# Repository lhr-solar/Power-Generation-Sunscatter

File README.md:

# :sunny: Sunscatter - Maximum Power Point Tracker Board

- [:sunny: Sunscatter - Maximum Power Point Tracker Board](#sunny-sunscatter---maximum-power-point-tracker-board)
  - [Repository Structure](#repository-structure)
  - [Maintainers](#maintainers)
  - [Versioning](#versioning)
  - [TODO](#todo)

---

## Repository Structure

- **datasheets** - contains datasheets for major components of the Sunscatter.
- **docs** - contains documentation on how to build, test, and use the Sunscatter.
- **fw** - contains fw that is loaded onto the Sunscatter.
  - **tests** - test programs used to characterize and validate the Sunscatter.
  - **src** - main program used to run the Sunscatter.
  - **inc** - internally developed libraries specific for the Sunscatter.
  - **lib** - third party libraries used by the Sunscatter.
- **hw**
  - **Footprints** - project specfic footprint association files for the Sunscatter.
  - **Models** - 3d .step files for the PCB 3d viewer.
  - **Symbols** - project specific symbol files for the Sunscatter.
  - **vX_Y_Z** - frozen versioning folder for PCB production files.
  - design files

---

## Maintainers

The current maintainer of this project is Matthew Yu as of 07/16/2023. His email
is [matthewjkyu@gmail.com](matthewjkyu@gmail.com).

Contributors to the HW and FW encompass many dedicated students, including:

- Jacob Pustilnik
- Afnan Mir
- Youssef Elsherif
- Austin Tsao
- Joseph Onofre
- Ricky Tiet
- Javier Lopez
- Chioma Okorie
- Corey Hulse
- Kaleb Todd
- Jennifer Dahm
- And many others...

Special thanks to Professor Gary Hallock, who supervised the development and
design of this project.

---

## Versioning

This PCB is on unified version `3.4.0`. Every time the schematic and/or layout
is updated, this version number should go up. We use [semantic
versioning](https://semver.org/) to denote between versions. See the
[changelog](./docs/CHANGELOG.md) for more details.

---

## TODO

Documentation

- Update assembly and testing document, ordering document, and improvement document.
- Add datasheets for key components of the device.

HW

- Transition to v4.0.0 using modified board design from MPPT-design repo
- Clean up files in hw folder

SW

- Regenerate code for MBED with proposed filestructure

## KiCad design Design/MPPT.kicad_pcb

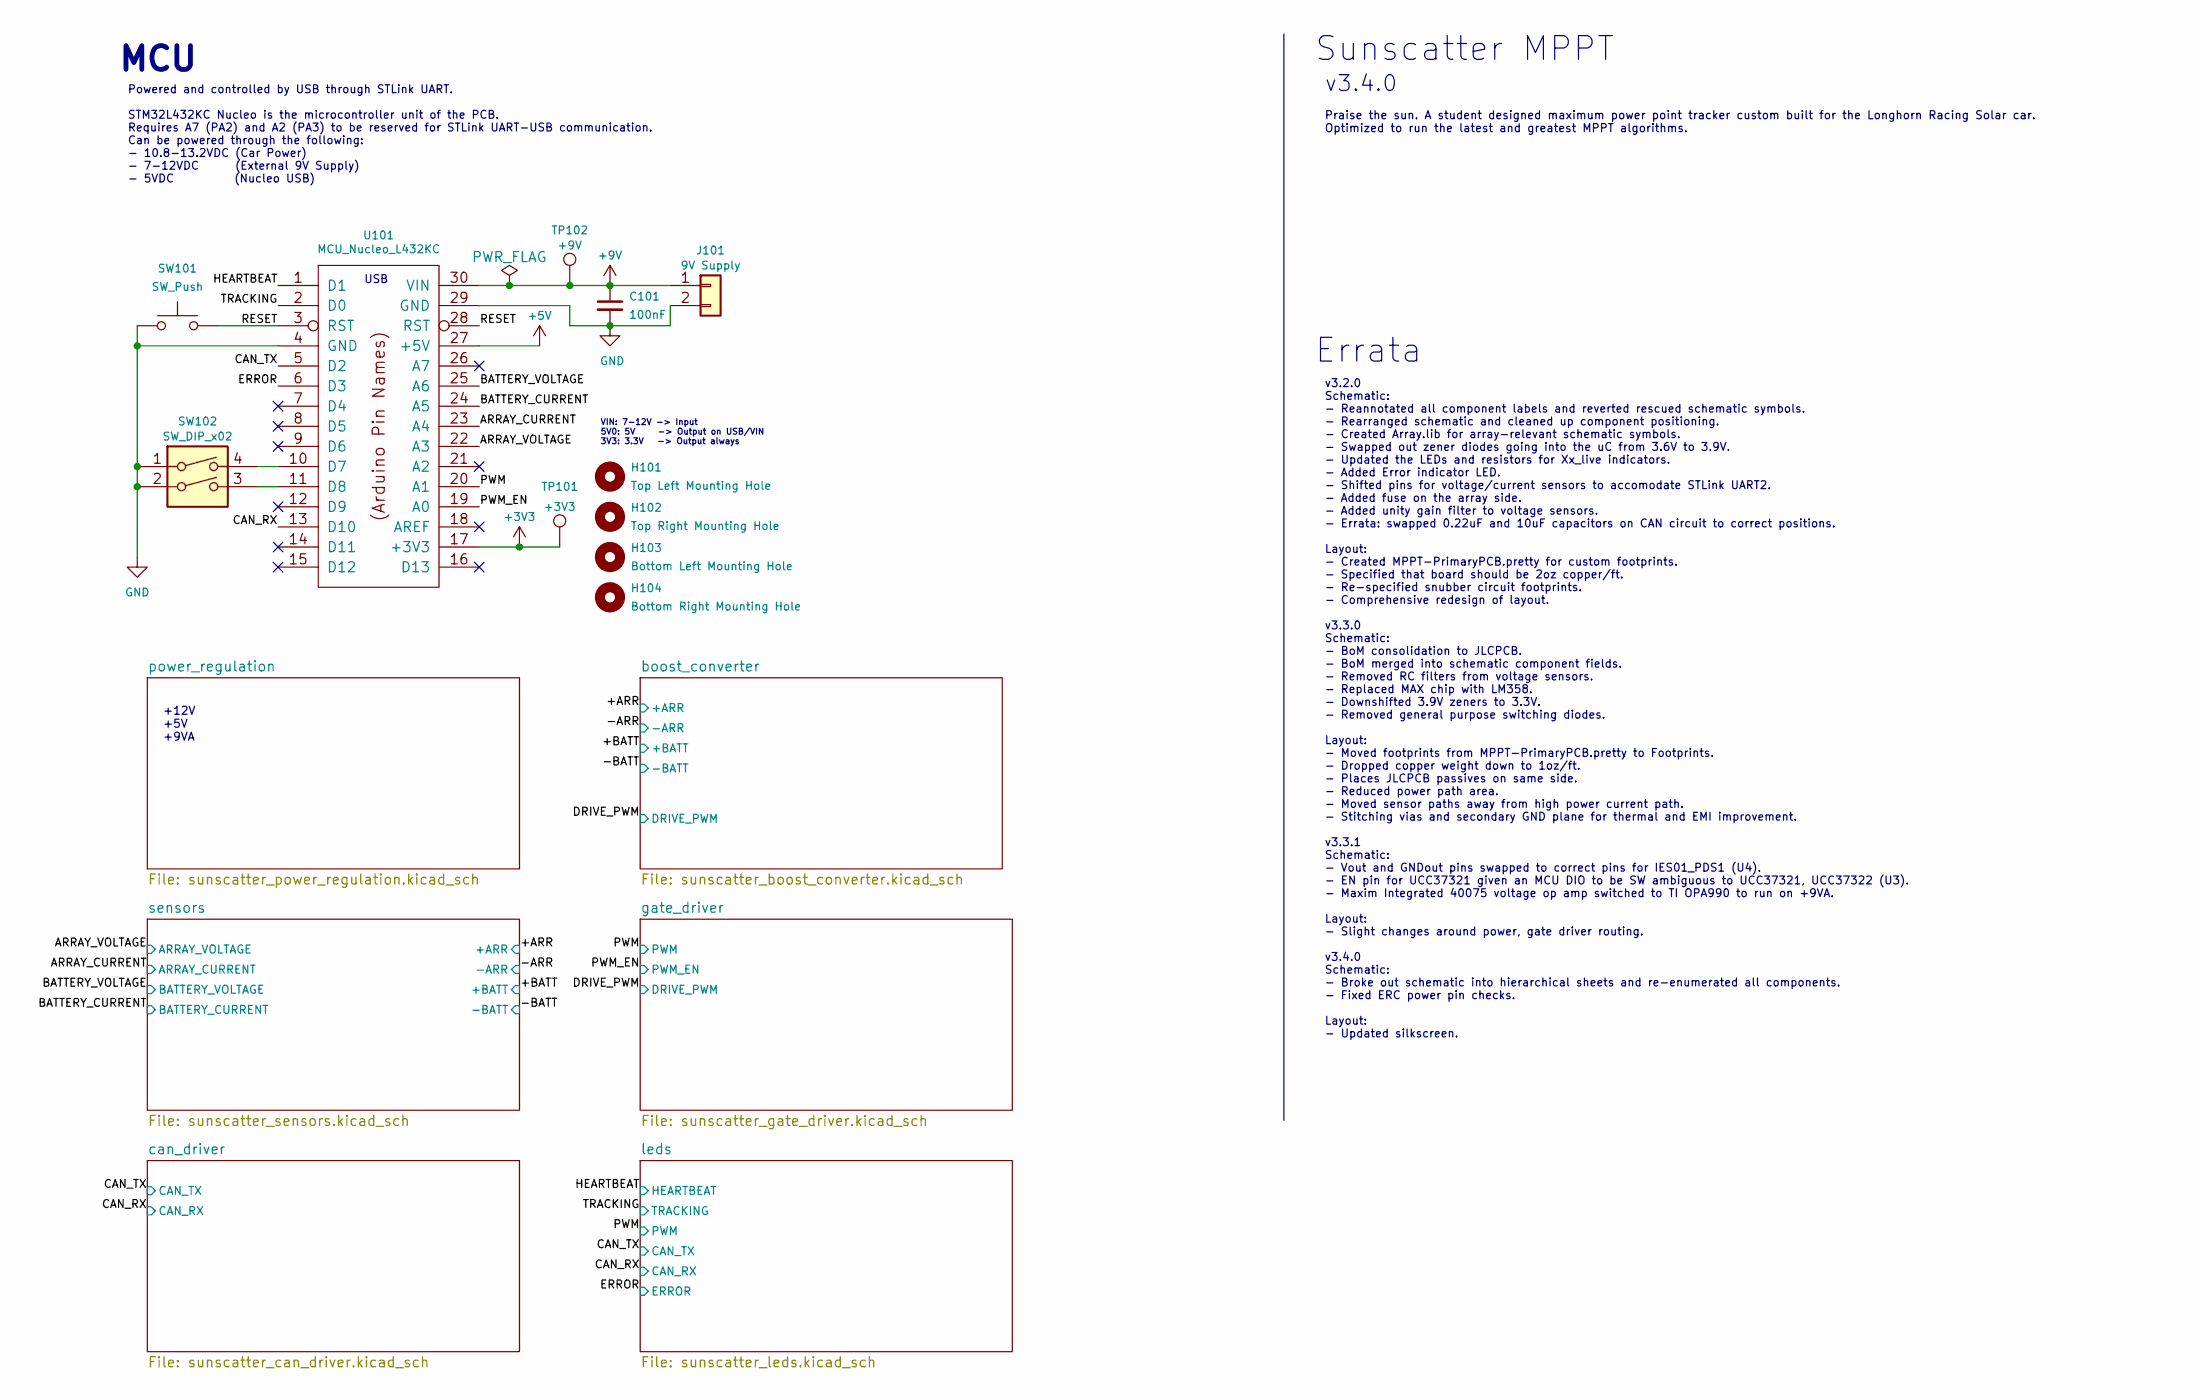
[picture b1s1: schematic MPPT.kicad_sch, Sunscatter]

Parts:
C101: 100nF; C_0805_2012Metric; Manufacturer Part Number CL21B104KCFNNNE; JLCPCB BOM 1
H101: Top Left Mounting Hole; MountingHole_3.2mm_M3
H102: Top Right Mounting Hole; MountingHole_3.2mm_M3
H103: Bottom Left Mounting Hole; MountingHole_3.2mm_M3
H104: Bottom Right Mounting Hole; MountingHole_3.2mm_M3
J101: 9V Supply; Molex_Micro-Fit_3.0_43650-0215_1x02_P3.00mm_Vertical; Manufacturer Part Number 43650-0215; JLCPCB BOM 0
SW101: SW_Push; SW_PUSH_6mm; Manufacturer Part Number TS02-66-50-BK-260-SCR-D; JLCPCB BOM 0
SW102: SW_DIP_x02; ADF02ST04_DIP_Switch_2_POS; Manufacturer Part Number ADF02ST04; JLCPCB BOM 0
TP101: +3V3; TestPoint_Pad_1.0x1.0mm
TP102: +9V; TestPoint_Pad_1.0x1.0mm
U101: MCU_Nucleo_L432KC; MODULE_NUCLEO-L432KC; Manufacturer Part Number 511-NUCLEO-L432KC; JLCPCB BOM 0

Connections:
+5V: U101.27 (+5V); also elsewhere on the board
+9V: C101.1, J101.1, TP102.1, U101.30 (VIN)
/ARRAY_CURRENT: U101.23 (A4); also elsewhere on the board
/ARRAY_VOLTAGE: U101.22 (A3); also elsewhere on the board
/BATTERY_CURRENT: U101.24 (A5); also elsewhere on the board
/BATTERY_VOLTAGE: U101.25 (A6); also elsewhere on the board
/CAN_RX: U101.13 (D10); also elsewhere on the board
/CAN_TX: U101.5 (D2); also elsewhere on the board
/ERROR: U101.6 (D3); also elsewhere on the board
/HEARTBEAT: U101.1 (D1); also elsewhere on the board
/PWM: U101.20 (A1); also elsewhere on the board
/PWM_EN: U101.19 (A0); also elsewhere on the board
/RESET: SW101.2, U101.3 (RST), U101.28 (RST)
/TRACKING: U101.2 (D0); also elsewhere on the board
GND: C101.2, J101.2, SW101.1, SW102.1, SW102.2, U101.4 (GND), U101.29 (GND); also elsewhere on the board
unnamed: SW102.3, U101.11 (D8)
unnamed: SW102.4, U101.10 (D7)

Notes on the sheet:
Errata
VIN: 7-12V -> Input 5V0: 5V -> Output on USB/VIN 3V3: 3.3V -> Output always
USB
v3.2.0 Schematic: - Reannotated all component labels and reverted rescued schematic symbols. - Rearranged schematic and cleaned up component positioning. - Created Array.lib for array-relevant schematic symbols. - Swapped out zener diodes going into the uC from 3.6V to 3.9V. - Updated the LEDs and 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
v3.4.0
Powered and controlled by USB through STLink UART. STM32L432KC Nucleo is the microcontroller unit of the PCB. Requires A7 (PA2) and A2 (PA3) to be reserved for STLink UART-USB communication. Can be powered through the following: - 10.8-13.2VDC (Car Power) - 7-12VDC (External 9V Supply) - 5VDC (Nucl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
MCU
Sunscatter MPPT
+12V +5V +9VA
Praise the sun. A student designed maximum power point tracker custom built for the Longhorn Racing Solar car. Optimized to run the latest and greatest MPPT algorithms.

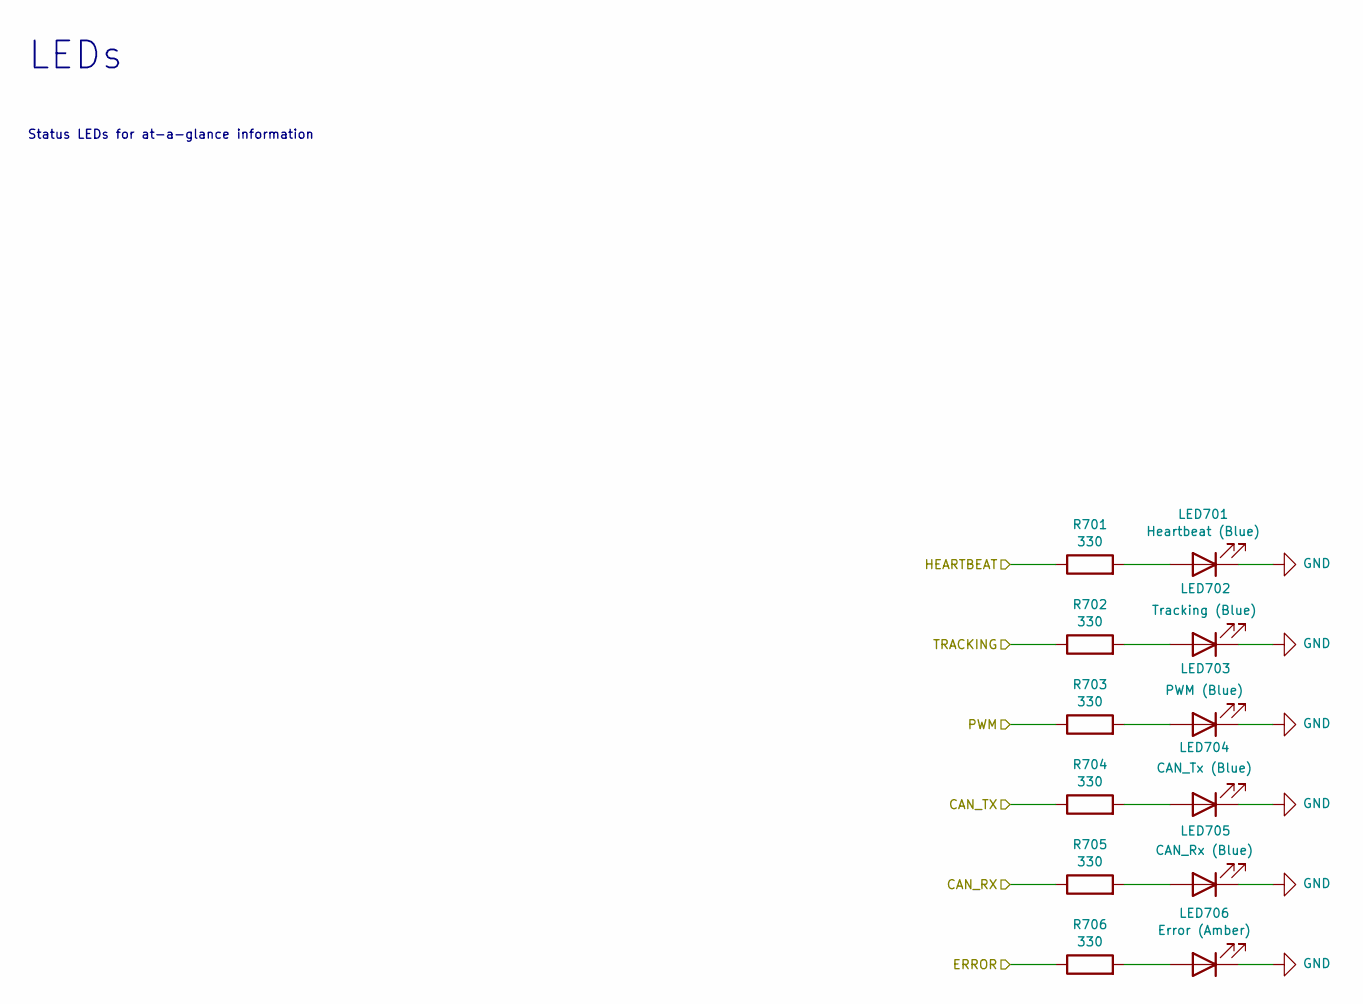
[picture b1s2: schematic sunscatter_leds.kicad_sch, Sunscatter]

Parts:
LED701: Heartbeat (Blue); LED_0805_2012Metric; Manufacturer Part Number APTD2012LQBC/D; JLCPCB BOM 0
LED702: Tracking (Blue); LED_0805_2012Metric; Manufacturer Part Number APTD2012LQBC/D; JLCPCB BOM 0
LED703: PWM (Blue); LED_0805_2012Metric; Manufacturer Part Number APTD2012LQBC/D; JLCPCB BOM 0
LED704: CAN_Tx (Blue); LED_0805_2012Metric; Manufacturer Part Number APTD2012LQBC/D; JLCPCB BOM 0
LED705: CAN_Rx (Blue); LED_0805_2012Metric; Manufacturer Part Number APTD2012LQBC/D; JLCPCB BOM 0
LED706: Error (Amber); LED_0805_2012Metric; Manufacturer Part Number APTD2012LSURCK; JLCPCB BOM 0
R701, R702, R703, R704, R705, R706: 330; R_0805_2012Metric; Manufacturer Part Number 0805W8F3300T5E; JLCPCB BOM 1

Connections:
/CAN_RX: R705.1; also elsewhere on the board
/CAN_TX: R704.1; also elsewhere on the board
/ERROR: R706.1; also elsewhere on the board
/HEARTBEAT: R701.1; also elsewhere on the board
/PWM: R703.1; also elsewhere on the board
/TRACKING: R702.1; also elsewhere on the board
GND: LED701.1 (K), LED702.1 (K), LED703.1 (K), LED704.1 (K), LED705.1 (K), LED706.1 (K); also elsewhere on the board
unnamed: LED701.2 (A), R701.2
unnamed: LED702.2 (A), R702.2
unnamed: LED703.2 (A), R703.2
unnamed: LED704.2 (A), R704.2
unnamed: LED705.2 (A), R705.2
unnamed: LED706.2 (A), R706.2

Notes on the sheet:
Status LEDs for at-a-glance information
LEDs

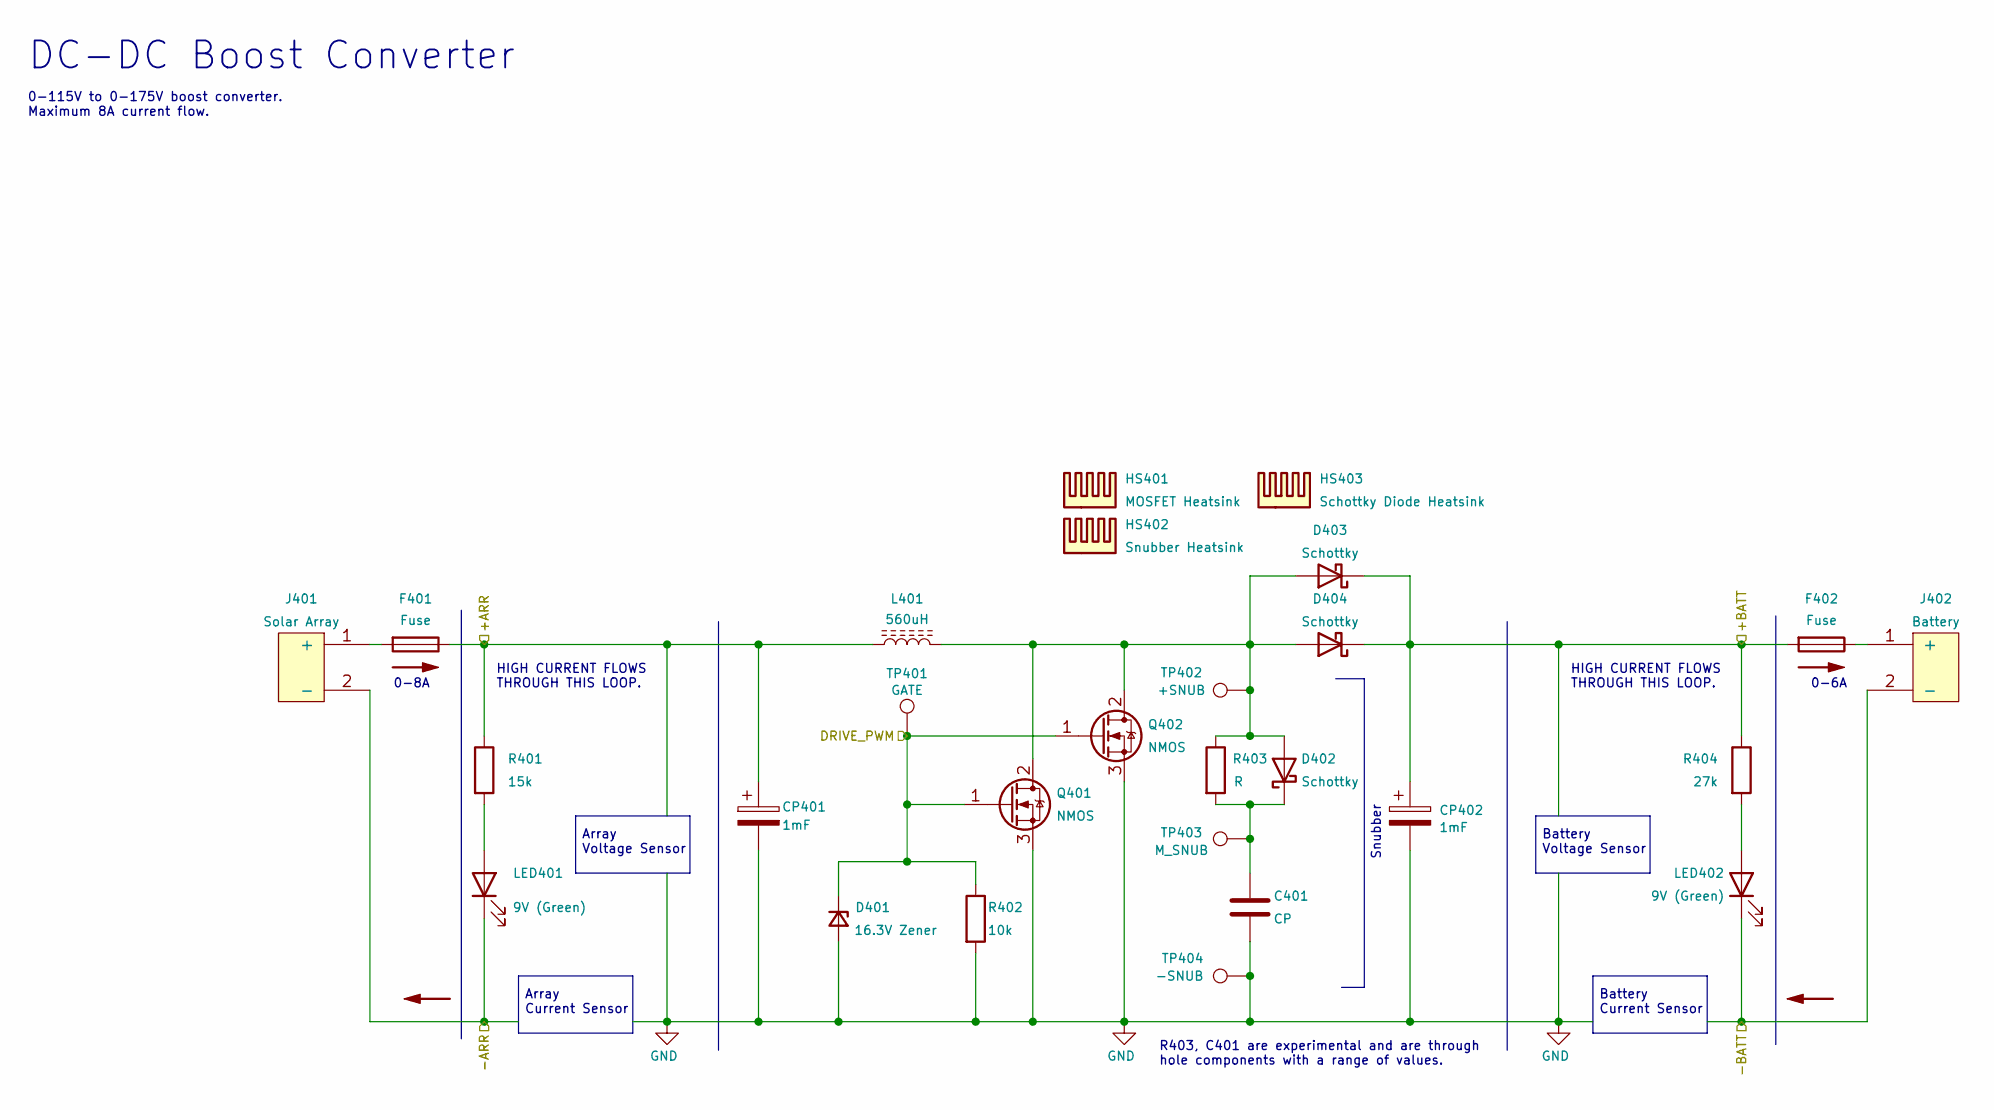
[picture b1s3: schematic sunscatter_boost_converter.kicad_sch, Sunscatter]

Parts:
C401: CP; C_Rect_L16.5mm_W7.0mm_P15.00mm_MKT; Mouser Part 75-MKT1813247635; JLCPCB BOM 0
CP401, CP402: 1mF; CP_Radial_D30.0mm_P10.00mm_SnapIn; Manufacturer Part Number SLPX102M250E5P3; JLCPCB BOM 0
D401: 16.3V Zener; D_SOD-123F; Manufacturer Part Number BZT52H-B16,115; JLCPCB BOM 0
D402, D403, D404: Schottky; TO-220-2_Vertical; Manufacturer Part Number SCS308AHGC9; JLCPCB BOM 0
F401, F402: Fuse; 05200101Z_Fuze_Holder_5x20_PCB_Mount; Manufacturer Part Number 05200101Z; JLCPCB BOM 0
HS401: MOSFET Heatsink; Heatsink_Fischer_SK129-STS_42x25mm_2xDrill2.5mm; Manufacturer Part Number FA-T220-38E; JLCPCB BOM 0
HS402: Snubber Heatsink; Heatsink_Fischer_SK129-STS_42x25mm_2xDrill2.5mm; Manufacturer Part Number FA-T220-38E; JLCPCB BOM 0
HS403: Schottky Diode Heatsink; Heatsink_Fischer_SK129-STS_42x25mm_2xDrill2.5mm; Manufacturer Part Number FA-T220-38E; JLCPCB BOM 0
J401: Solar Array; PhoenixContact_PowerCombicon5_GF_2x7.62mm; Manufacturer Part Number 1720796; JLCPCB BOM 0
J402: Battery; PhoenixContact_PowerCombicon5_GF_2x7.62mm; Manufacturer Part Number 1720796; JLCPCB BOM 0
L401: 560uH; L_Toroid_Vertical_L46.0mm_W19.1mm_P21.80mm_Bourns_5700; Manufacturer Part Number HF400-601M-8.0AV; JLCPCB BOM 0
LED401, LED402: 9V (Green); LED_0805_2012Metric; Manufacturer Part Number APTD2012LCGCK; JLCPCB BOM 0
Q401, Q402: NMOS; TO-247-3_Vertical; Manufacturer Part Number IXFH80N65X2; JLCPCB BOM 0
R401: 15k; R_0805_2012Metric; Manufacturer Part Number 0805W8F1502T5E; JLCPCB BOM 1
R402: 10k; R_0805_2012Metric; Manufacturer Part Number 0805W8F1002T5E; JLCPCB BOM 1
R403: R; TO-220-2_Vertical; Manufacturer Part Number PWR220T-35-33R0J; JLCPCB BOM 0
R404: 27k; R_0805_2012Metric; Manufacturer Part Number 0805W8F2702T5E; JLCPCB BOM 1
TP401: GATE; TestPoint_Pad_1.0x1.0mm
TP402: +SNUB; TestPoint_Pad_1.0x1.0mm
TP403: M_SNUB; TestPoint_Pad_1.0x1.0mm
TP404: -SNUB; TestPoint_Pad_1.0x1.0mm

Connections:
/+ARR: CP401.1, F401.1, L401.1, R401.1; also elsewhere on the board
/+BATT: CP402.1, D403.1 (K), D404.1 (K), F402.2, R404.1; also elsewhere on the board
/-ARR: J401.2 (-), LED401.1 (K); also elsewhere on the board
/-BATT: J402.2 (-), LED402.1 (K); also elsewhere on the board
/DRIVE_PWM: D401.1 (K), Q401.1 (G), Q402.1 (G), R402.1, TP401.1; also elsewhere on the board
GND: C401.2, CP401.2, CP402.2, D401.2 (A), Q401.3 (S), Q402.3 (S), R402.2, TP404.1; also elsewhere on the board
unnamed: C401.1, D402.1 (K), R403.2, TP403.1
unnamed: D402.2 (A), D403.2 (A), D404.2 (A), L401.2, Q401.2 (D), Q402.2 (D), R403.1, TP402.1
unnamed: F401.2, J401.1 (+)
unnamed: F402.1, J402.1 (+)
unnamed: LED401.2 (A), R401.2
unnamed: LED402.2 (A), R404.2

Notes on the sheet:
DC-DC Boost Converter
Array Voltage Sensor
HIGH CURRENT FLOWS THROUGH THIS LOOP.
R403, C401 are experimental and are through hole components with a range of values.
0-115V to 0-175V boost converter. Maximum 8A current flow.
0-8A
0-6A
Battery Current Sensor
Array Current Sensor
Battery Voltage Sensor
Snubber

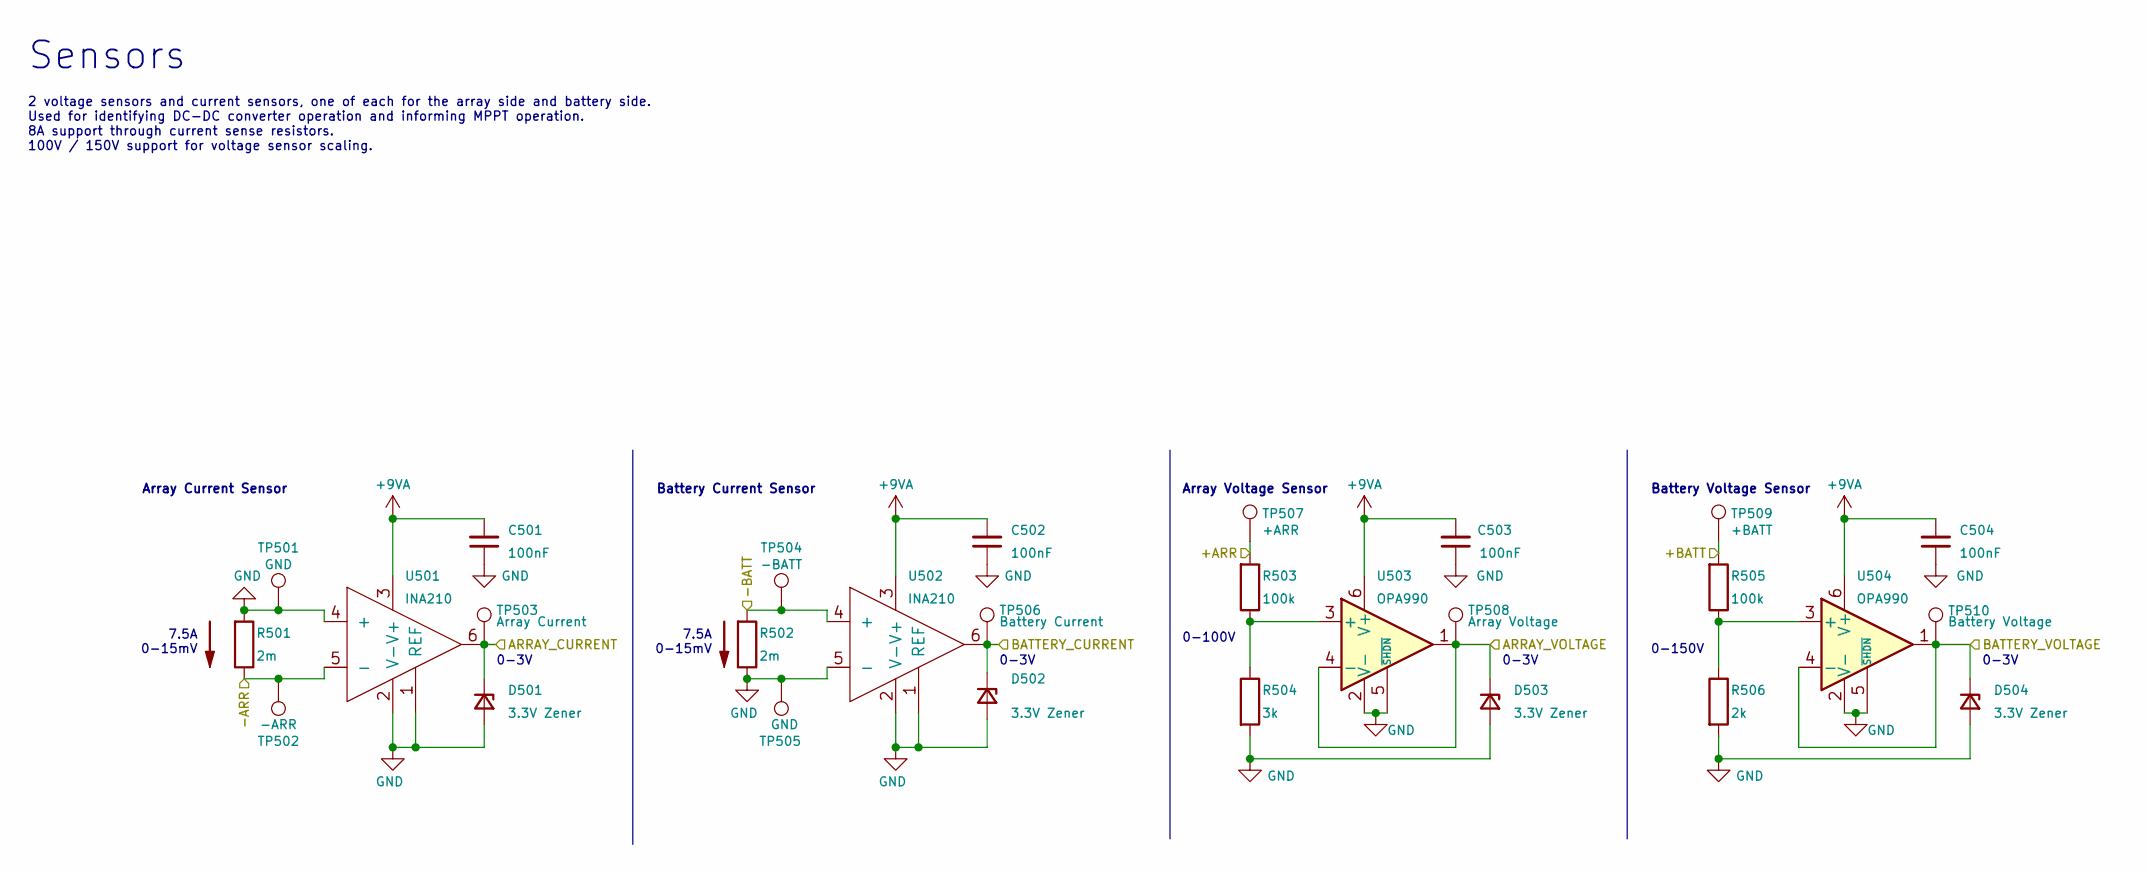
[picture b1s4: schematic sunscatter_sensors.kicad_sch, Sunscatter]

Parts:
C501, C502, C503, C504: 100nF; C_0805_2012Metric; Manufacturer Part Number CL21B104KCFNNNE; JLCPCB BOM 1
D501, D502, D503, D504: 3.3V Zener; D_MiniMELF; Manufacturer Part Number ZMM3V3-M; JLCPCB BOM 1
R501, R502: 2m; R_1206_3216Metric; Manufacturer Part Number PMR18EZPFV2L00; JLCPCB BOM 0
R503, R505: 100k; R_0805_2012Metric; Manufacturer Part Number 0805W8F1003T5E; JLCPCB BOM 1
R504: 3k; R_0805_2012Metric; Manufacturer Part Number 0805W8F3001T5E; JLCPCB BOM 1
R506: 2k; R_0805_2012Metric; Manufacturer Part Number 0805W8F2001T5E; JLCPCB BOM 1
TP501, TP505: GND; TestPoint_Pad_1.0x1.0mm
TP502: -ARR; TestPoint_Pad_1.0x1.0mm
TP503: Array Current; TestPoint_Pad_1.0x1.0mm
TP504: -BATT; TestPoint_Pad_1.0x1.0mm
TP506: Battery Current; TestPoint_Pad_1.0x1.0mm
TP507: +ARR; TestPoint_Pad_1.0x1.0mm
TP508: Array Voltage; TestPoint_Pad_1.0x1.0mm
TP509: +BATT; TestPoint_Pad_1.0x1.0mm
TP510: Battery Voltage; TestPoint_Pad_1.0x1.0mm
U501, U502: INA210; SOT-363_SC-70-6_Handsoldering; Manufacturer Part Number INA210AIDCKT; JLCPCB BOM 0
U503, U504: OPA990; SOT-23-6; Manufacturer Part Number OPA990SIDBVR; JLCPCB BOM 0

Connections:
+9VA: C501.2, C502.2, C503.2, C504.2, U501.3 (V+), U502.3 (V+), U503.6 (V+), U504.6 (V+); also elsewhere on the board
/+ARR: R503.2, TP507.1; also elsewhere on the board
/+BATT: R505.2, TP509.1; also elsewhere on the board
/-ARR: R501.1, TP502.1, U501.5 (-); also elsewhere on the board
/-BATT: R502.2, TP504.1, U502.4 (+); also elsewhere on the board
/ARRAY_CURRENT: D501.1 (K), TP503.1, U501.6; also elsewhere on the board
/ARRAY_VOLTAGE: D503.1 (K), TP508.1, U503.1, U503.4 (-); also elsewhere on the board
/BATTERY_CURRENT: D502.1 (K), TP506.1, U502.6; also elsewhere on the board
/BATTERY_VOLTAGE: D504.1 (K), TP510.1, U504.1, U504.4 (-); also elsewhere on the board
GND: C501.1, C502.1, C503.1, C504.1, D501.2 (A), D502.2 (A), D503.2 (A), D504.2 (A), R501.2, R502.1, R504.2, R506.2, TP501.1, TP505.1, U501.1 (REF), U501.2 (V-), U501.4 (+), U502.1 (REF), U502.2 (V-), U502.5 (-), U503.2 (V-), U503.5 (~SHDN), U504.2 (V-), U504.5 (~SHDN); also elsewhere on the board
unnamed: R503.1, R504.1, U503.3 (+)
unnamed: R505.1, R506.1, U504.3 (+)

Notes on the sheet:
0-3V
7.5A 0-15mV
Array Current Sensor
Array Voltage Sensor
0-150V
2 voltage sensors and current sensors, one of each for the array side and battery side. Used for identifying DC-DC converter operation and informing MPPT operation. 8A support through current sense resistors. 100V / 150V support for voltage sensor scaling.
Sensors
Battery Current Sensor
Battery Voltage Sensor
0-100V

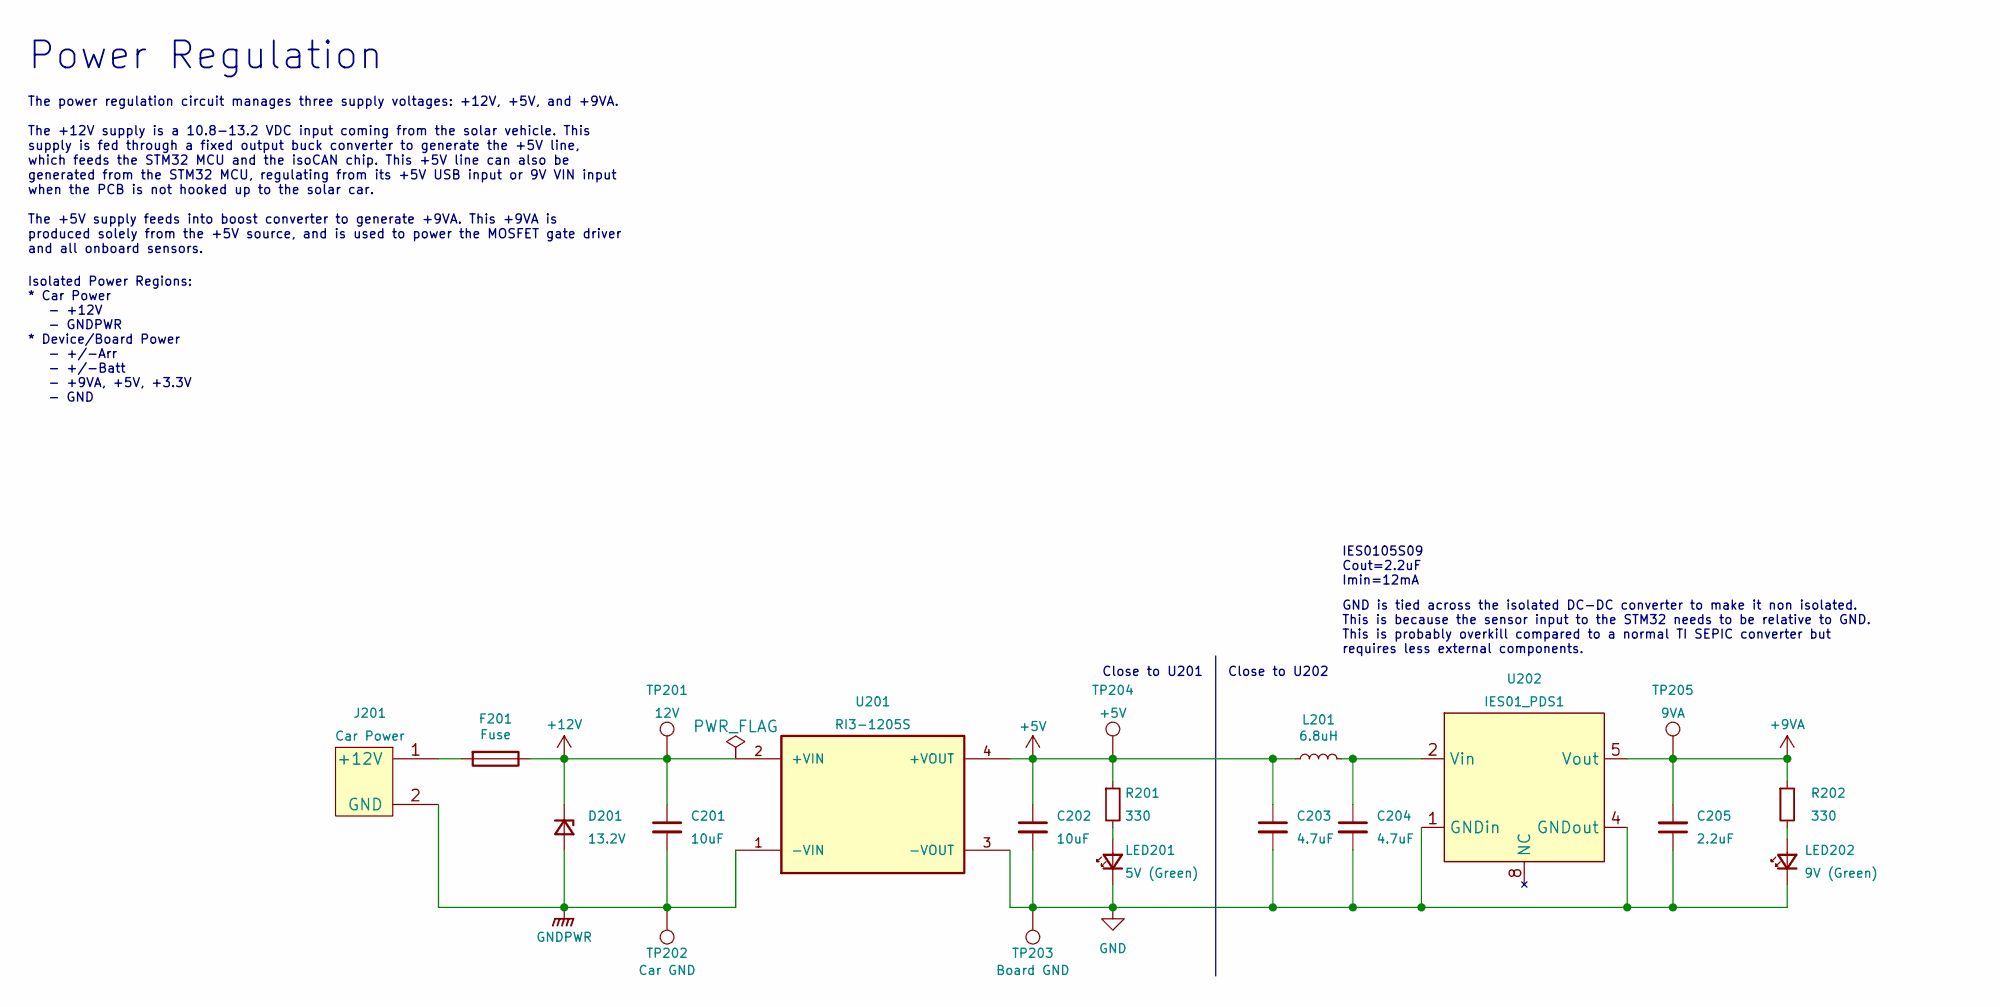
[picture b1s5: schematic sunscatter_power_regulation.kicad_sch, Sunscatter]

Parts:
C201, C202: 10uF; C_0805_2012Metric; Manufacturer Part Number CL21A106KAYNNNE; JLCPCB BOM 1
C203, C204: 4.7uF; C_0805_2012Metric; Manufacturer Part Number CL21A475KAQNNNE; JLCPCB BOM 1
C205: 2.2uF; C_0805_2012Metric; Manufacturer Part Number 0805F225M500NT; JLCPCB BOM 1
D201: 13.2V; D_SOD-323F; Manufacturer Part Number PZU13B2,115; JLCPCB BOM 0
F201: Fuse; 05200101Z_Fuze_Holder_5x20_PCB_Mount; Manufacturer Part Number 05200101Z; JLCPCB BOM 0
J201: Car Power; Molex_Micro-Fit_3.0_43650-0215_1x02_P3.00mm_Vertical; Manufacturer Part Number 43650-0215; JLCPCB BOM 0
L201: 6.8uH; L_Taiyo-Yuden_NR-50xx; Manufacturer Part Number NRS5040T6R8MMGJ; JLCPCB BOM 0
LED201: 5V (Green); LED_0805_2012Metric; Manufacturer Part Number APTD2012LCGCK; JLCPCB BOM 0
LED202: 9V (Green); LED_0805_2012Metric; Manufacturer Part Number APTD2012LCGCK; JLCPCB BOM 0
R201, R202: 330; R_0805_2012Metric; Manufacturer Part Number 0805W8F3300T5E; JLCPCB BOM 1
TP201: 12V; TestPoint_Pad_1.0x1.0mm
TP202: Car GND; TestPoint_Pad_1.0x1.0mm
TP203: Board GND; TestPoint_Pad_1.0x1.0mm
TP204: +5V; TestPoint_Pad_1.0x1.0mm
TP205: 9VA; TestPoint_Pad_1.0x1.0mm
U201: RI3-1205S; CONV_RI3-1205S; Manufacturer Part Number RI3-1205S; JLCPCB BOM 0
U202: IES01_PDS1; Manufacturer Part Number IES0105S09; JLCPCB BOM 0

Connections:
+5V: C202.1, C203.1, L201.1, R201.1, TP204.1, U201.4 (+VOUT); also elsewhere on the board
+9VA: C205.2, R202.1, TP205.1, U202.5 (Vout); also elsewhere on the board
+12V: C201.1, D201.1 (K), F201.1, TP201.1, U201.2 (+VIN)
GND: C202.2, C203.2, C204.2, C205.1, LED201.1 (K), LED202.1 (K), TP203.1, U201.3 (-VOUT), U202.1 (GNDin), U202.4 (GNDout); also elsewhere on the board
GNDPWR: C201.2, D201.2 (A), J201.2 (GND), TP202.1, U201.1 (-VIN)
unnamed: C204.1, L201.2, U202.2 (Vin)
unnamed: F201.2, J201.1 (+12V)
unnamed: LED201.2 (A), R201.2
unnamed: LED202.2 (A), R202.2

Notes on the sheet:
Close to U202
IES0105S09 Cout=2.2uF Imin=12mA
The power regulation circuit manages three supply voltages: +12V, +5V, and +9VA. The +12V supply is a 10.8-13.2 VDC input coming from the solar vehicle. This supply is fed through a fixed output buck converter to generate the +5V line, which feeds the STM32 MCU and the isoCAN chip. This +5V line ca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
Power Regulation
Isolated Power Regions: * Car Power - +12V - GNDPWR * Device/Board Power - +/-Arr - +/-Batt - +9VA, +5V, +3.3V - GND
Close to U201
GND is tied across the isolated DC-DC converter to make it non isolated. This is because the sensor input to the STM32 needs to be relative to GND. This is probably overkill compared to a normal TI SEPIC converter but requires less external components.

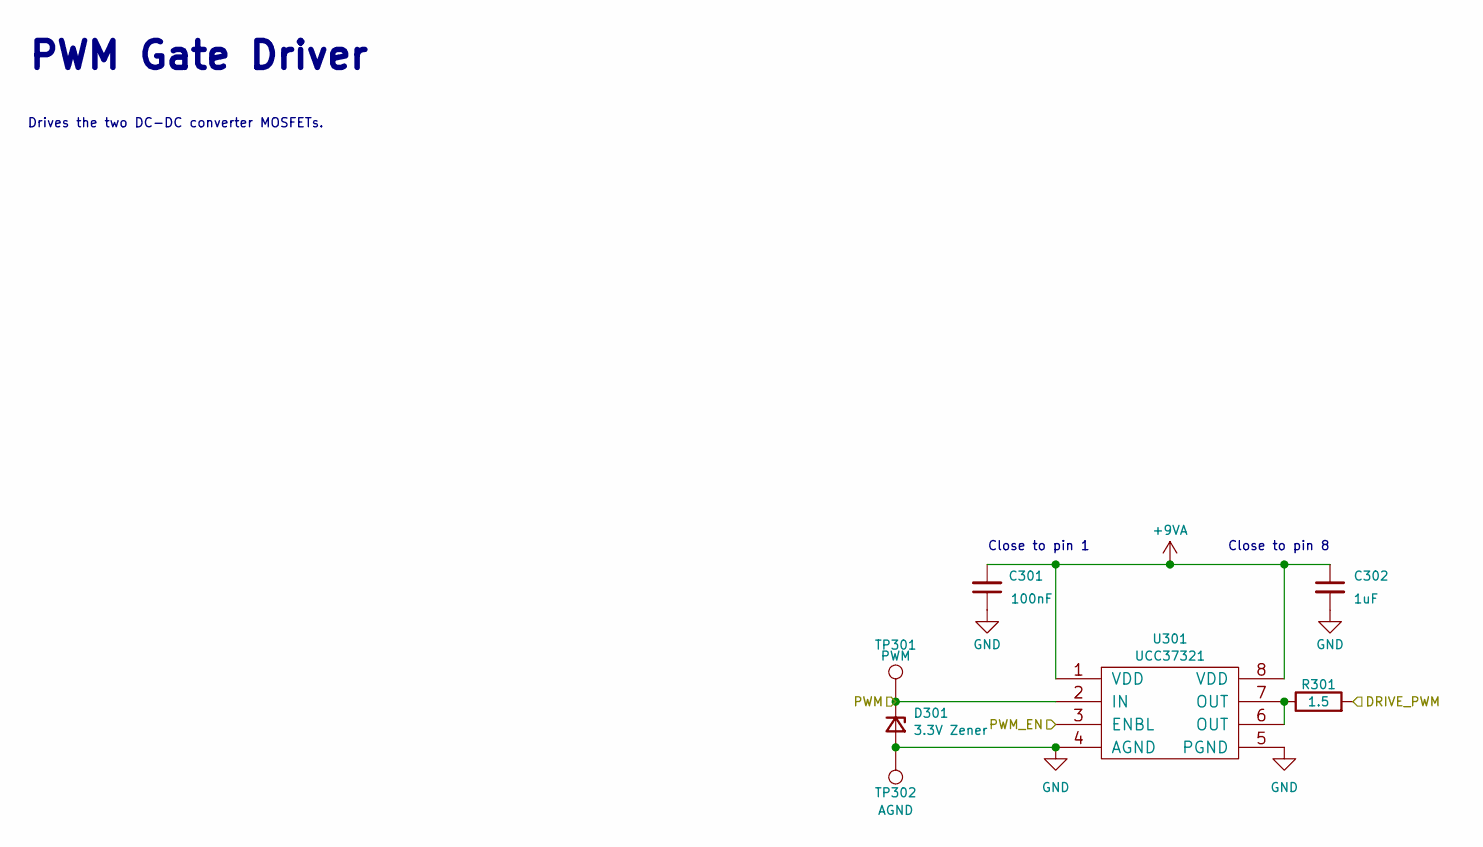
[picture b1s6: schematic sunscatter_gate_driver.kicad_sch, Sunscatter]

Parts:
C301: 100nF; C_0805_2012Metric; Manufacturer Part Number CL21B104KCFNNNE; JLCPCB BOM 1
C302: 1uF; C_0805_2012Metric; Manufacturer Part Number CL21B105KBFNNNE; JLCPCB BOM 1
D301: 3.3V Zener; D_MiniMELF; Manufacturer Part Number ZMM3V3-M; JLCPCB BOM 1
R301: 1.5; R_0805_2012Metric; Manufacturer Part Number CRCW08051R50FKEAHP; JLCPCB BOM 0
TP301: PWM; TestPoint_Pad_1.0x1.0mm
TP302: AGND; TestPoint_Pad_1.0x1.0mm
U301: UCC37321; SOIC-8_3.9x4.9mm_P1.27mm; Manufacturer Part Number UCC37321D; JLCPCB BOM 0

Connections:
+9VA: C301.2, C302.1, U301.1 (VDD), U301.8 (VDD); also elsewhere on the board
/DRIVE_PWM: R301.2; also elsewhere on the board
/PWM: D301.1 (K), TP301.1, U301.2 (IN); also elsewhere on the board
/PWM_EN: U301.3 (ENBL); also elsewhere on the board
GND: C301.1, C302.2, D301.2 (A), TP302.1, U301.4 (AGND), U301.5 (PGND); also elsewhere on the board
unnamed: R301.1, U301.6 (OUT), U301.7 (OUT)

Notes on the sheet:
Drives the two DC-DC converter MOSFETs.
Close to pin 1
PWM Gate Driver
Close to pin 8

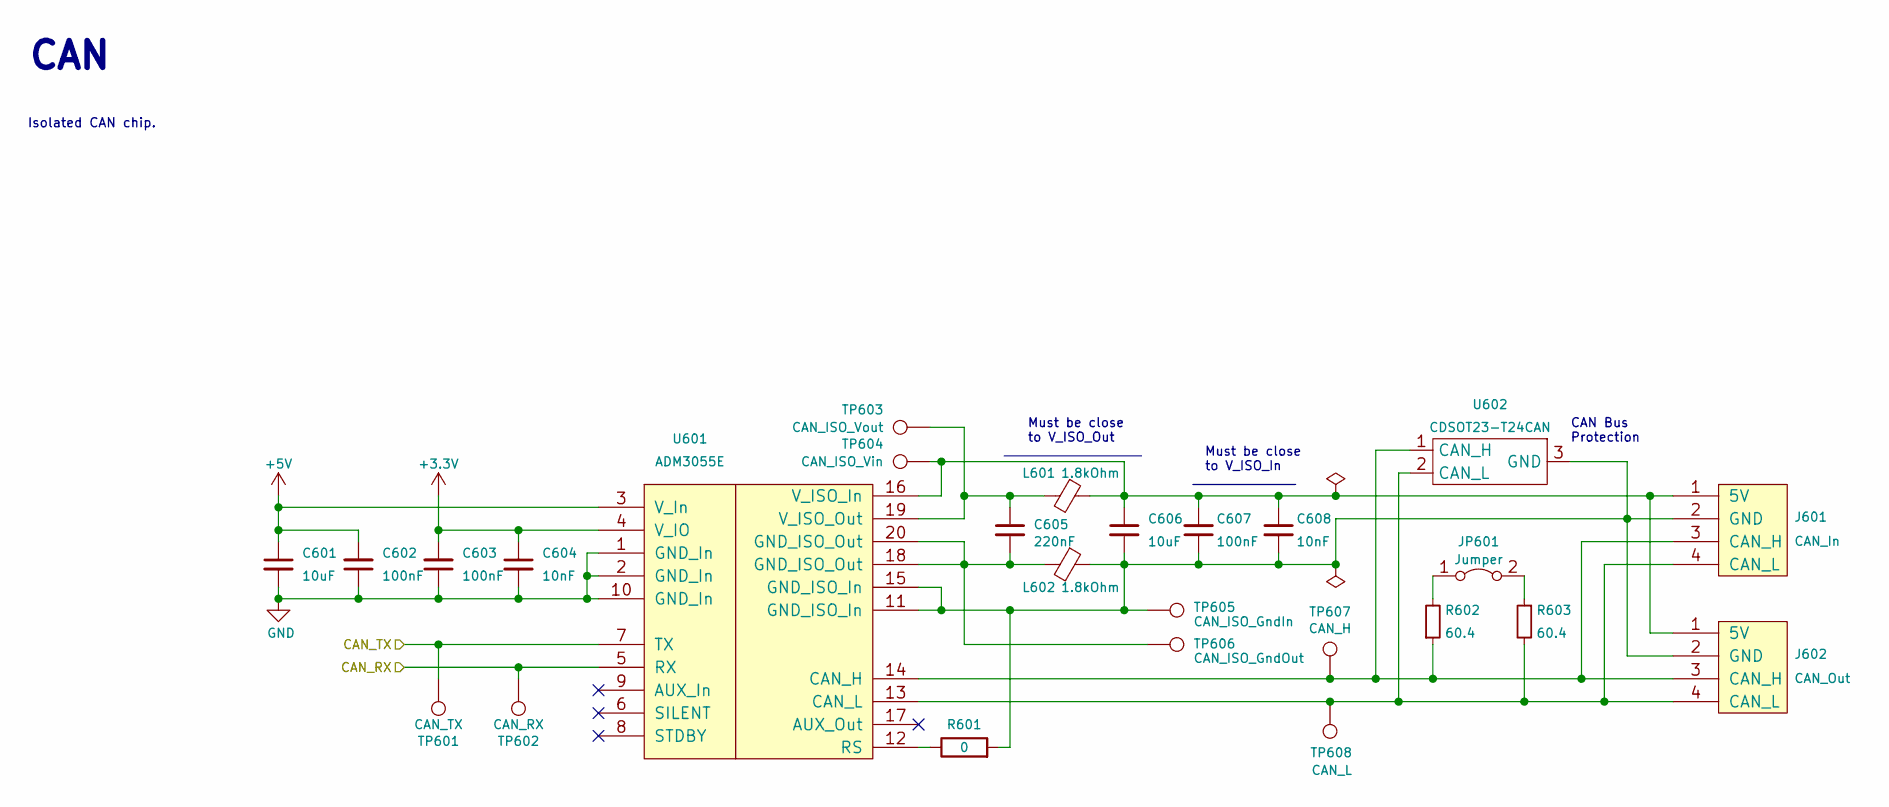
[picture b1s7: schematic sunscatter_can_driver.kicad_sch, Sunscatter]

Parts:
C601, C606: 10uF; C_0805_2012Metric; Manufacturer Part Number CL21A106KAYNNNE; JLCPCB BOM 1
C602, C603, C607: 100nF; C_0805_2012Metric; Manufacturer Part Number CL21B104KCFNNNE; JLCPCB BOM 1
C604, C608: 10nF; C_0805_2012Metric; Manufacturer Part Number CL21B103KBANNNC; JLCPCB BOM 1
C605: 220nF; C_0805_2012Metric; Manufacturer Part Number CL21B224KBFNNNE; JLCPCB BOM 1
J601: CAN_In; Molex_Micro-Fit_3.0_43650-0415_1x04_P3.00mm_Vertical; Manufacturer Part Number 43650-0427; JLCPCB BOM 0
J602: CAN_Out; Molex_Micro-Fit_3.0_43650-0415_1x04_P3.00mm_Vertical; Manufacturer Part Number 43650-0427; JLCPCB BOM 0
JP601: Jumper; PinHeader_1x02_P2.54mm_Vertical
L601, L602: 1.8kOhm; L_0805_2012Metric; Manufacturer Part Number BLM21BD182SN1D; JLCPCB BOM 0
R601: 0; R_0805_2012Metric; Manufacturer Part Number 0805W8F0000T5E; JLCPCB BOM 1
R602, R603: 60.4; R_0805_2012Metric; Manufacturer Part Number CRCW080560R4FKEAHP; JLCPCB BOM 0
TP601: CAN_TX; TestPoint_Pad_1.0x1.0mm
TP602: CAN_RX; TestPoint_Pad_1.0x1.0mm
TP603: CAN_ISO_Vout; TestPoint_Pad_1.0x1.0mm
TP604: CAN_ISO_Vin; TestPoint_Pad_1.0x1.0mm
TP605: CAN_ISO_GndIn; TestPoint_Pad_1.0x1.0mm
TP606: CAN_ISO_GndOut; TestPoint_Pad_1.0x1.0mm
TP607: CAN_H; TestPoint_Pad_1.0x1.0mm
TP608: CAN_L; TestPoint_Pad_1.0x1.0mm
U601: ADM3055E; ADM3055EBRIZ; Manufacturer Part Number ADM3055EBRIZ; JLCPCB BOM 0
U602: CDSOT23-T24CAN; SOT-23; Manufacturer Part Number CDSOT23-T24CAN-Q; JLCPCB BOM 0

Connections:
+5V: C601.1, C602.2, U601.3 (V_In); also elsewhere on the board
/CAN_RX: TP602.1, U601.5 (RX); also elsewhere on the board
/CAN_TX: TP601.1, U601.7 (TX); also elsewhere on the board
GND: C601.2, C602.1, C603.1, C604.2, U601.1 (GND_In), U601.2 (GND_In), U601.10 (GND_In); also elsewhere on the board
unnamed: C605.1, L601.2, TP603.1, U601.19 (V_ISO_Out)
unnamed: C605.2, L602.2, TP606.1, U601.18 (GND_ISO_Out), U601.20 (GND_ISO_Out)
unnamed: C606.1, C607.2, C608.1, J601.1 (5V), J602.1 (5V), L601.1, TP604.1, U601.16 (V_ISO_In)
unnamed: C606.2, C607.1, C608.2, J601.2 (GND), J602.2 (GND), L602.1, R601.2, TP605.1, U601.11 (GND_ISO_In), U601.15 (GND_ISO_In), U602.3 (GND)
unnamed: J601.3 (CAN_H), J602.3 (CAN_H), R602.1, TP607.1, U601.14 (CAN_H), U602.1 (CAN_H)
unnamed: J601.4 (CAN_L), J602.4 (CAN_L), R603.2, TP608.1, U601.13 (CAN_L), U602.2 (CAN_L)
unnamed: JP601.1 (A), R602.2
unnamed: JP601.2 (B), R603.1
unnamed: R601.1, U601.12 (RS)

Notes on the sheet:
CAN Bus Protection
CAN
Must be close to V_ISO_Out
Isolated CAN chip.
Must be close to V_ISO_In

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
